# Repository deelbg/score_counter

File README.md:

# score_counter

[Also available on my online store.](https://www.tindie.com/stores/deyantodorov/)

  Board games Score Counter is a device meant to be used for keeping the score for up to four players when playing board games like Scrabble etc. The numbers of players is selectable through the settings menu. Names up to ten characters long can be entered for each player.
  For each player an accumulated score is stored, which is the total amount of points up to the current moment in the game, and the points from the current round are entered using a rotary encoder or the Up and Down arrow keys. When OK is pressed the point from the current round are added to the total amount. 
  More detailed explanation and screenshot might be found in the User manual [HERE](https://github.com/deelbg/score_counter/blob/master/sc_manual.pdf) or on my web site [HERE](https://deyantodorov.com/2020/06/24/board-games-score-counter/)
  
Main features.
* Small size (10cm / 5.5cm / 1.7cm). 
* Battery powered. Runs on two AAA batteries.
* 1.3” OLED screen.
* Controlled via five buttons and a rotary switch.
* 3D printed enclosure.
* Energy independent memory to store settings and player names.

In the **/firmware** directory is located the firmware. It uses the drivers from my [SSD1306_SH1106_i2c_text_display](https://github.com/deelbg/SSD1306_SH1106_i2c_text_display) and [hal_lib_avr_cpp](https://github.com/deelbg/hal_lib_avr_cpp) repositories. 
The device is based on a Attiny861 microcontroller.

There is a makefile included. Run the folowing:
* make - to build the project
* clean - to delete object files
* size - to see the used RAM and flash.
* flash - to write the .hex file to the microcontroller. Using avrdude and a usbasp programmer.
* eeprom - to write the eeprom.
* fuse - to write the fuses.

In the **/hardware** directory is located the hardware project for EagleCad and a KiCad export. 
**NOTE:** A 10kOhm pullup resistor needs to be added to the OK button (the one right in the center).  

In the **/enclosure** directory is located a FreeCad project containig the enclosure. The 3 parts are also exported in .obj files that can be directly imported in Cura and sliced for 3d printing.

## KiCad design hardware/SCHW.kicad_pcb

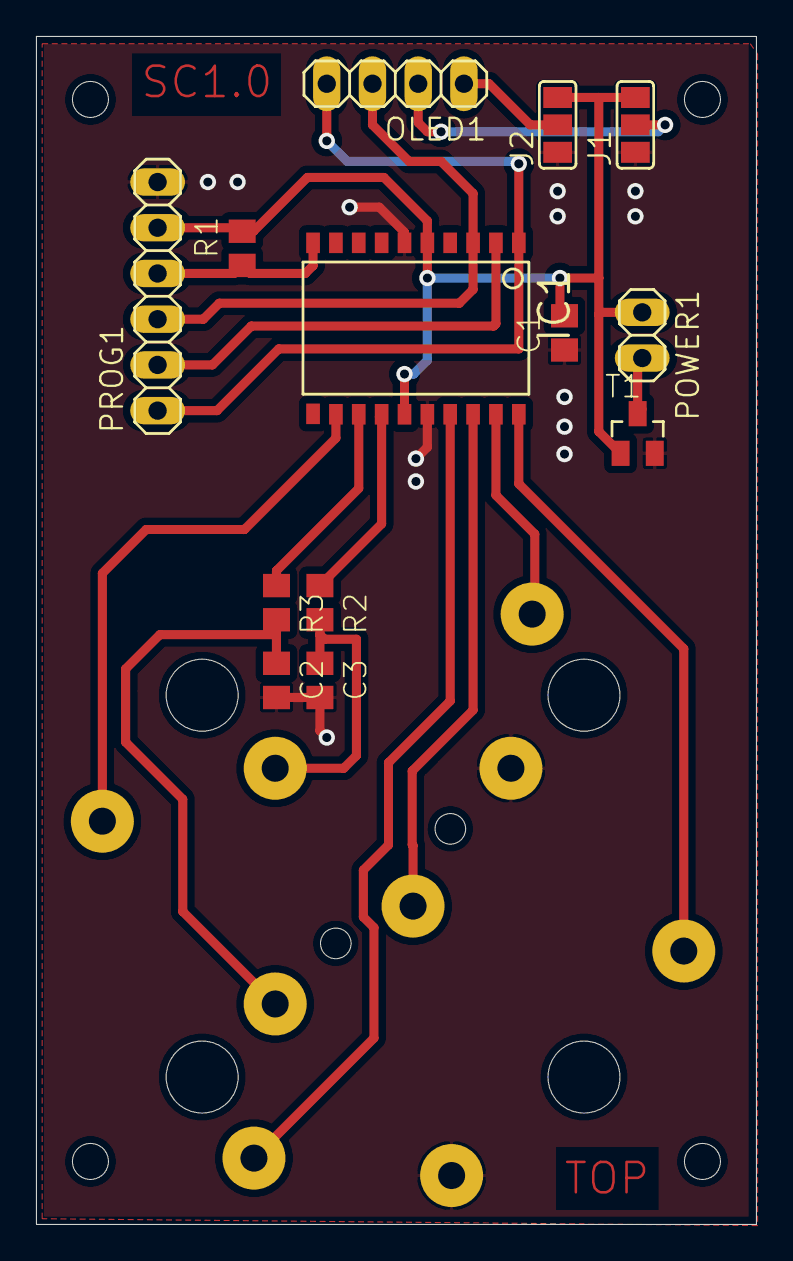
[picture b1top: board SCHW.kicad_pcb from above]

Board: 2 copper layers, 40.0 x 66.0 mm, 18 parts (0 on the bottom side), 17 nets.

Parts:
@HOLE0, @HOLE1, @HOLE2, @HOLE3: (no value)
BUTTONS1: ENCODER_ARROWS
C1, C2, C3: 100n; C0805
IC1: TINY26S; SO20L
J1, J2: SJ2W; SJ_2
OLED1: PINHD-1X4; 1X04
POWER1: PINHD-1X2; 1X02
PROG1: PINHD-1X6; 1X06
R1: 10k; R0805
R2, R3: 10K; R0805
T1: AP2306GN_MOSFETSOT23; SOT23

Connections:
/SCHW_1/DOWN: BUTTONS1.S2, IC1.17
/SCHW_1/ENC_A: BUTTONS1.A, C2.1, R3.2
/SCHW_1/ENC_A_RAW: IC1.13, R3.1
/SCHW_1/ENC_B: BUTTONS1.B, C3.1, R2.2
/SCHW_1/ENC_B_RAW: IC1.14, R2.1
/SCHW_1/LEFT: BUTTONS1.S5, IC1.20
/SCHW_1/MISO: IC1.2, PROG1.2
/SCHW_1/MOSI/SDA: IC1.1, OLED1.4, PROG1.1
/SCHW_1/OK: BUTTONS1.S1, IC1.18
/SCHW_1/RESET: IC1.10, PROG1.4, R1.1
/SCHW_1/RIGHT: BUTTONS1.S3, IC1.12
/SCHW_1/SCK: IC1.3, OLED1.3, PROG1.3
/SCHW_1/UP: BUTTONS1.S4, IC1.19
GND: BUTTONS1.COM_A, BUTTONS1.COM_B, C1.1, C2.2, C3.2, IC1.6, IC1.16, J1.1, J2.1, PROG1.6, T1.2
unnamed: J1.2, OLED1.2
unnamed: J2.2, OLED1.1
VCC: C1.2, IC1.5, IC1.15, J1.3, J2.3, POWER1.1, PROG1.5, R1.2

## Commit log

2020-06-25 Score counter, hardware, software and enclosure v1.0
2020-06-25 Add build and dist directtories including the .hx file.
2020-06-26 Add the user manual sc_manual.pdf.
